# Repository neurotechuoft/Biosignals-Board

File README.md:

# Biosignals-Board

## Overview

The goal of this project is to build an EEG (electroencephalogram) signal acquisition pipeline for the "Fixed Challenge" portion of the NeurotechX Student competition taking place on March 18, 2018. The pipeline will consist of a biosignals board that is capable of picking up an analog EEG signal, perform analog to digital conversion and signal processing, and transmit the signal to a distant computer for real-time visualization and other applications.

### NeurotechX Competition Specifications

1. [Competition Website](https://neurotechx.github.io/studentclubs/competition/ "NeurotechX Competition")

## Project Plan
We will be developing during the summer and fall of 2017, targetting project completion by the end of 2017, leaving 3 months for additional testing and building upon the competition-ready project. The project is being organized into three subsections: analog signal acquistion and amplification, analog to digital conversion, and data transmission/software, which will all be developed concurrently. For analog to digital conversion, we will be using the Texas Instruments [ADS1299 ADC chip](./code/digital/README.md) to convert the acquired EEG signal.

## Project Progress
* Developed high-level schematic of entire system

## Excellent Resources
* [EEG PocketGuide](https://drive.google.com/file/d/0B4xsbDIeDmLPY3hObm1DVjV1TmM/view?usp=sharing)

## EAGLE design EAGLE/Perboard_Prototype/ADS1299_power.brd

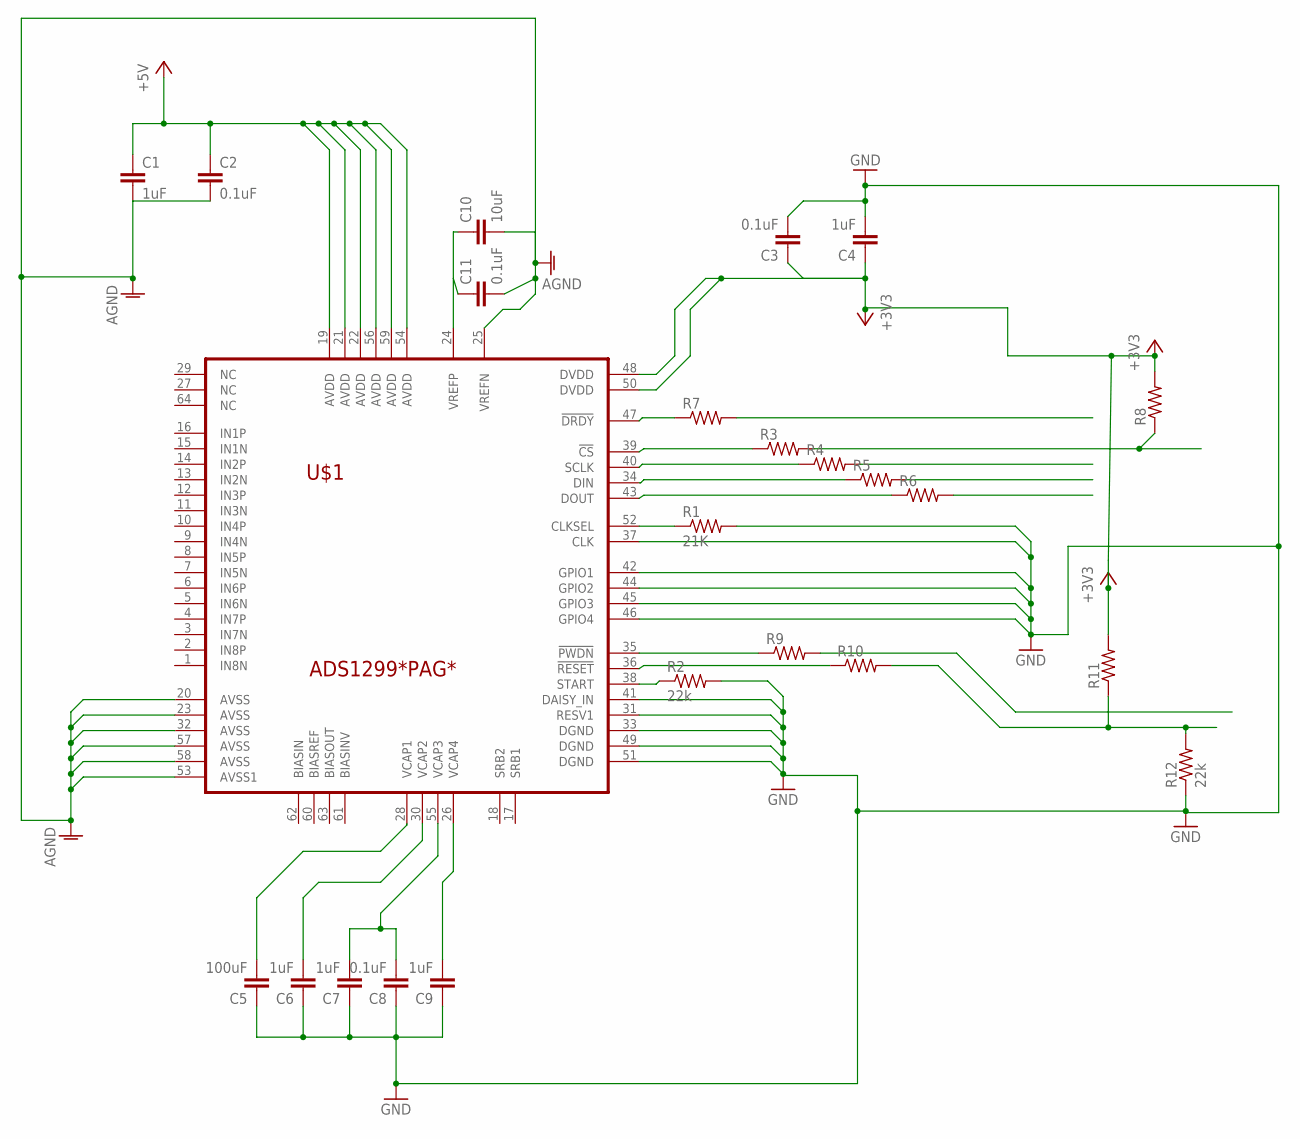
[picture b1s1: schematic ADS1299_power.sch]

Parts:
C1, C4, C6, C7, C9: 1uF; C2.5-3
C2, C3, C8, C11: 0.1uF; C2.5-3
C5: 100uF; C2.5-3
C10: 10uF; C2.5-3
R1: 21K; 0204V
R2, R12: 22k; 0204V
R3, R4, R5, R6, R7, R8, R9, R10, R11: R-US_0204/2V; 0204V
U$1: ADS1299*PAG*; TQFP64

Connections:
+3V3: C3.1, C4.1, R8.2, R11.2, U$1.48 (DVDD), U$1.50 (DVDD)
+5V: C1.1, C2.1, U$1.19 (AVDD), U$1.21 (AVDD), U$1.22 (AVDD), U$1.54 (AVDD), U$1.56 (AVDD), U$1.59 (AVDD)
AGND: C1.2, C2.2, C10.2, C11.2, U$1.20 (AVSS), U$1.23 (AVSS), U$1.25 (VREFN), U$1.32 (AVSS), U$1.53 (AVSS1), U$1.57 (AVSS), U$1.58 (AVSS)
GND: C3.2, C4.2, C5.1, C6.1, C7.1, C8.1, C9.1, R1.2, R2.2, R12.1, U$1.31 (RESV1), U$1.33 (DGND), U$1.37 (CLK), U$1.41 (DAISY_IN), U$1.42 (GPIO1), U$1.44 (GPIO2), U$1.45 (GPIO3), U$1.46 (GPIO4), U$1.49 (DGND), U$1.51 (DGND)
unnamed: C9.2, U$1.26 (VCAP4)
unnamed: C7.2, C8.2, U$1.55 (VCAP3)
unnamed: C10.1, C11.1, U$1.24 (VREFP)
unnamed: R1.1, U$1.52 (CLKSEL)
unnamed: C5.2, U$1.28 (VCAP1)
unnamed: R3.1, U$1.39 (!CS)
unnamed: R4.1, U$1.40 (SCLK)
unnamed: C6.2, U$1.30 (VCAP2)
unnamed: R2.1, U$1.38 (START)
unnamed: R5.1, U$1.34 (DIN)
unnamed: R6.1, U$1.43 (DOUT)
unnamed: R3.2, R8.1
unnamed: R7.1, U$1.47 (!DRDY)
unnamed: R10.1, U$1.36 (!RESET)
unnamed: R9.1, U$1.35 (!PWDN)
unnamed: R10.2, R11.1, R12.2

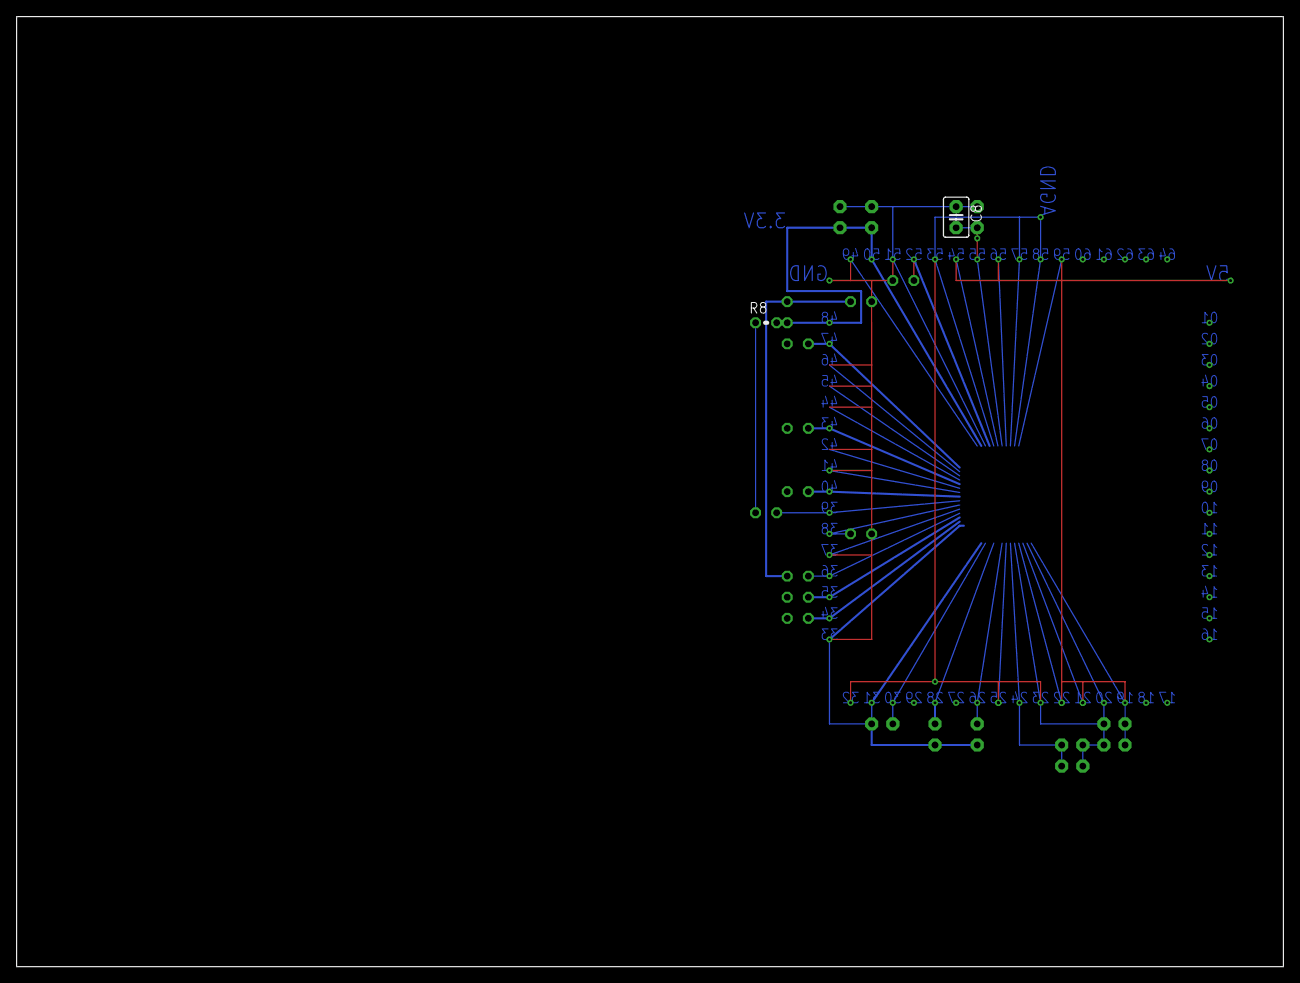
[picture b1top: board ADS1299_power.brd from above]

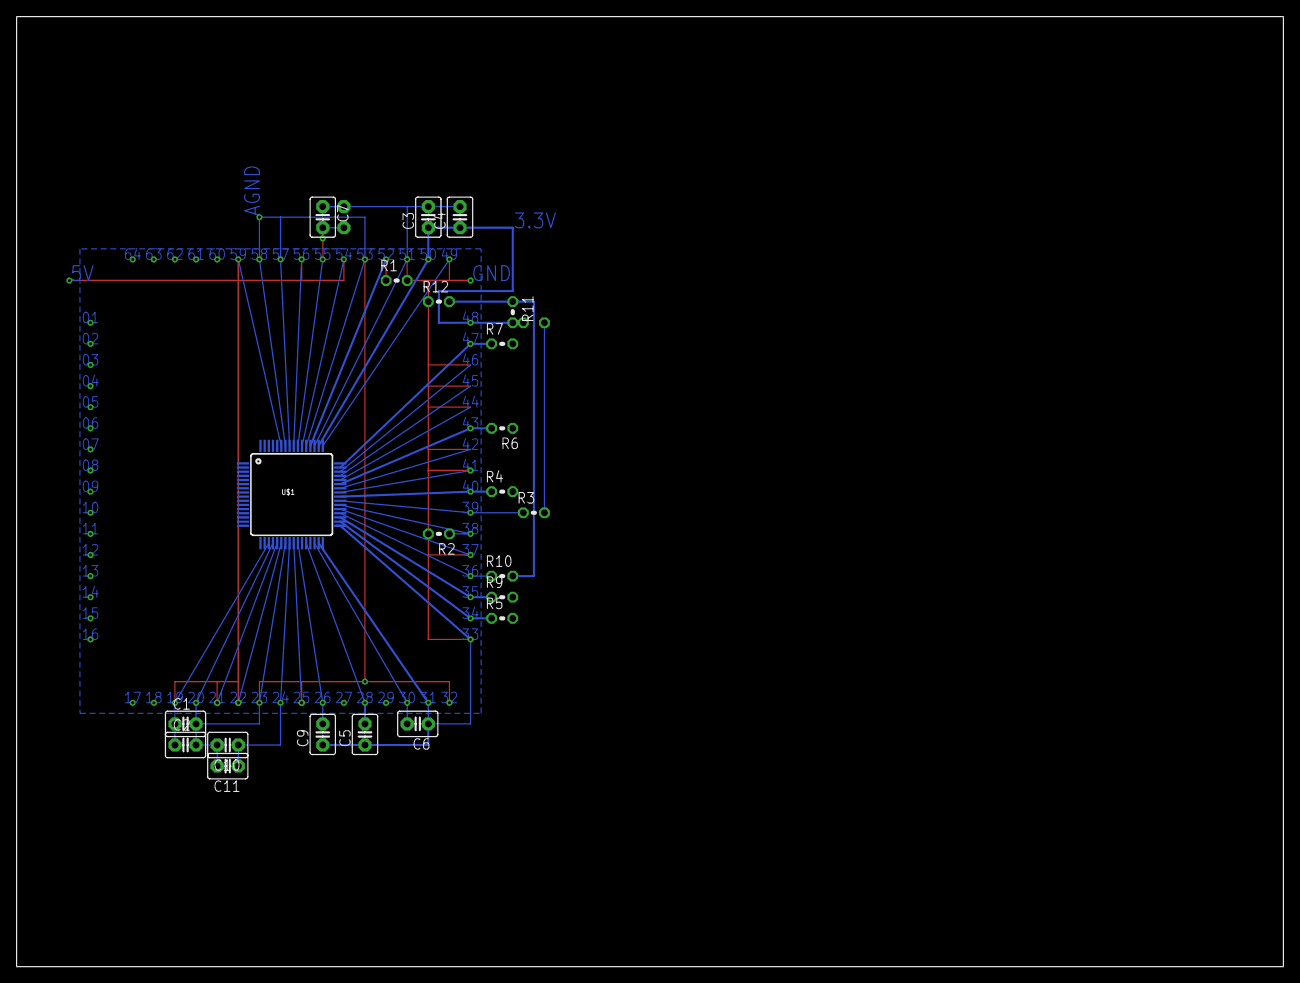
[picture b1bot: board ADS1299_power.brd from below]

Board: 2 copper layers, 152.4 x 114.3 mm, 24 parts (22 on the bottom side), 20 nets.

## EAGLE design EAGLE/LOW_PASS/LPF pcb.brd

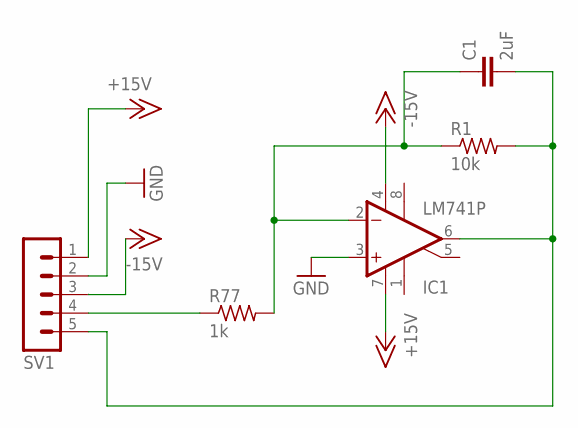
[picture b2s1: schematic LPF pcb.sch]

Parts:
C1: 2uF; C0603
IC1: LM741P; DIL08
R1: 10k; R0603
R77: 1k; R0603
SV1: MA05-1

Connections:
+15V: IC1.7 (V+), SV1.1
-15V: IC1.4 (V-), SV1.3
GND: IC1.3 (+IN), SV1.2
unnamed: R77.1, SV1.4
unnamed: C1.1, IC1.2 (-IN), R1.1, R77.2
unnamed: C1.2, IC1.6 (OUT), R1.2, SV1.5

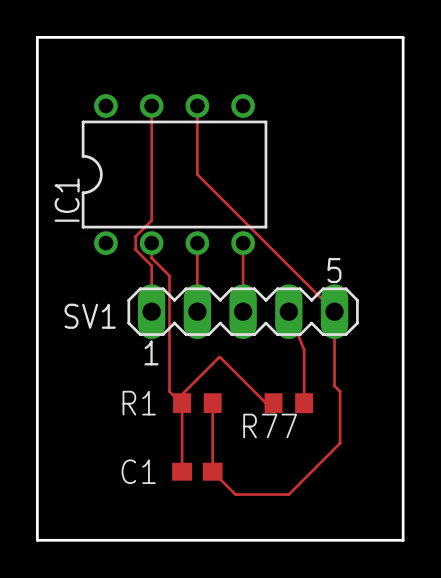
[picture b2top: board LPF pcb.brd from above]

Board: 2 copper layers, 20.3 x 27.9 mm, 5 parts (0 on the bottom side), 6 nets.

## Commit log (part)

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2016-10-05 Create New Folder
2016-10-06 Setting up a general overview and project plan. # Please enter the commit message for your changes. Lines starting # with '#' will be ignored, and an empty message aborts the commit. # # Committer: O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
2016-10-06 Setting up the overview structure for the project
2016-10-06 Formating overview design and adding TGAM section
2016-10-06 formatting
2016-10-06 Update README.md
    Future tasks
2016-10-06 attached arduino library for potential use
2016-10-06 Update README.md
    Documented all links from Oct. 5, 2016 meeting
2016-10-06 Meeting Notes updated
2016-10-08 Update README.md
    communications protocol
2016-11-01 Updating Project Progress
2016-11-15 testing bluetooth scanner
2016-11-15 added commenting
2017-04-03 Added requirements for 2017 competiton
2017-05-13 Updated competition rules link
2017-05-20 Repo update + planning schematic
2017-05-20 updated high level schematic
2017-05-20 showing image
2017-05-20 deleting old folders
2017-05-30 Updated meeting times
2017-06-01 updated meeting notes with tasks
2017-06-01 Pin and Register Config Spreadsheet
2017-06-01 organized files
2017-06-01 Organization of notes
2017-06-01 Passive filter hardware example
2017-06-01 added filter information
2017-06-01 Calculate frequency response + examples
2017-06-01 inculded EEG PocketGuide
2017-06-01 Passive Filter
2017-06-01 Included arduino signalgenerator
2017-06-01 included GoogleDrive link to EEG PocketGuide
2017-06-04 Added ADS1299 Arduino Library
2017-06-04 Modified .gitignore
2017-06-04 Deleted duplicate file Chip_Configuration.ods
2017-06-04 collapsed ADS1299 folder
2017-06-06 Filled in wiring connections for all pins
2017-06-06 Added more register information
2017-06-07 updated meeting notes
2017-06-08 Retrying previous commit: Added all pin connections
2017-06-08 Retrying commit: Added all wiring connections for all pins
2017-06-09 Removed ADS1299-Arduino library, will be replaced with OpenBCI Library
2017-06-09 Added OpenBCI ADS1299 Library
2017-06-09 updated meeting agendas
2017-06-10 restructure
2017-06-10 got rid of 2017 top folder
2017-06-10 Added code for bootup and converting test signal
2017-06-10 Updated .gitignore
2017-06-10 Implementign SPI on Arduino
2017-06-11 Reorganized pin chart and added diagram of pin connections
2017-06-11 Created Project_Timeline from General Meeting
2017-06-13 Added bootup and signal conversion code
2017-06-13 Arduinos communication
2017-06-17 Started agenda for Jun18 meeting
2017-06-17 Added resource for data transmission
2017-06-17 Re-formatted for Jun18 meeting agenda
2017-06-17 updated Raspberry Pi purchasing info
2017-06-18 Added to-do's to agenda
2017-06-18 Changed pin assignments to match our wiring
2017-06-18 Modified bootup code
2017-06-20 Updated Digital README
2017-06-20 Added meeting locations
2017-06-20 Started agenda for June 20 meeting
2017-06-20 Reformat meeting notes
2017-06-24 Added meeting notes for June 22
2017-06-28 Modified ADS1299 library to control PWDN pin and use Arduino SPI library
2017-06-28 Updated ads_bootup code to use modified ADS1299 library
2017-06-28 Recommiting ads_bootup, last commit not correct version
2017-06-29 Fixed bootup code
2017-06-30 Added June 28 meeting notes
2017-06-30 Updated meeting notes from June 17
2017-06-30 Added meeting notes for June 27
2017-07-02 Added functions for serial plotting and added our connections as defines in Definitions.h
2017-07-02 Experiment with Serial Plotter in Arduino IDE
2017-07-02 Added documentation and cleaned up code
2017-07-03 June 2nd session
2017-07-07 meeting Agenda for google Hangouts
2017-07-08 Updated meeting notes for July 7
2017-07-09 Started chart to track budget
2017-07-09 Started agenda for Sunday July 9 Meeting
2017-07-09 Added script to generate Meeting Notes template, work in progress
2017-07-09 updated TODOs
2017-07-09 included ##To-Do
2017-07-09 Cyton prog started doc
2017-07-11 Meeting notes for Design Studio
2017-07-19 notes from last meeting
2017-07-20 Naming
2017-07-23 Added summary of some key parameters and definitions in ADS1299 datasheet
2017-07-26 Added agenda and notes for Jul 26 meeting
2017-08-07 Moved and renamed Raspberry Pi Price research
2017-08-07 Fixed typos in pin connections
2017-08-07 Removed MicroSD card from 'To-buy' list and add to 'Purchased'
2017-08-07 Started Raspberry Pi Setup Notes
2017-08-08 Added ADSPacket class. This will be used when emulating ADS data
2017-08-08 Changed name of compiled executable
2017-08-08 Need to decide on meeting times
2017-08-09 Introductory meeting notes and next steps
2017-08-13 Meeting notes for Sunday Aug 13
2017-08-18 Started folder for hardware tests and added spi loopback test
2017-08-18 Reorganized RaspberryPi folder
2017-08-27 Add LPF Eagle project
2017-08-27 Removed LPF schematic.sch
2017-08-27 changed R2 to R77 made two reroutes
2017-08-28 Updated August 27 meeting notes
2017-08-30 Added ADS1299 datasheet for ease of access
2017-08-30 Updated pin connections in preparation for PCB
2017-08-31 Added meeting notes for Aug 30
2017-09-01 Minor updates to script
2017-09-03 Added section on default control register settings
2017-09-03 Started meeting notes for Sept 3
2017-09-03 Added ADS power schematic
2017-09-05 Updated meeting notes for Sept 03
2017-09-16 recruitment pdf
2017-09-17 Started meeting notes for September 17
2017-09-29 Renamed firmware folder to arduino-ads. Removed unused raspberrypi-ads library code
2017-09-29 Fixed incorrect data types
2017-09-29 Added comments and register descriptions
2017-10-02 Updaded schematic with open positions
2017-10-22 Reorganize repo - rename folders and files
2017-10-22 Reorganize repo: Move files into correct lib, src folders. Move analog, digital, and software folders under code/
2017-10-22 Move Musa's Arduino SPI code to src folder
2017-10-22 Added PDF version of competition rules
2017-10-23 Moved all previous meeting notes to the drive Converted from markdown to docx moved all scripts to admin/Summer2017/
2017-10-23 Restructured the code folder for Analog
2017-11-06 ADS1299_API bootup code
2017-11-07 Changed bootup delay time
2017-11-07 Implemented grid spacing. Added Frame. Need to route all the components
2017-11-08 Completed design for Protoboard Wiring.
2017-11-08 Re-wired pin 32 AGND
2017-11-09 Added .h file to .c
2017-11-09 Changed File Name
2017-11-09 Added .h file for ADS bcm bootup
2017-11-09 Fixed Minor Naming Error
2017-11-09 Updated EAGLE TODO and list of breakout pins
2017-11-10 Re-routed all sides and placed components on top
2017-11-11 Reorganized pins for breakout, differentiating perfboard and PCB
2017-11-11 Recomitting with latest version of BreakoutPins.txt
2017-11-12 Added register test function and reorganized functions to use ese519 library
2017-11-12 Moved main function from ADS1299_bcm2835 to main.c file
2017-11-12 Removed Meeting Notes section from README
2017-11-12 Add print statement for debuging
2017-11-12 Fix typo
2017-11-12 add carriage return
2017-11-13 restructure the code + modify makefile
2017-11-13 Fix function return type + Make File builds + completed source relocationing
2017-11-13 fixes compilation error
2017-11-13 add compatible bcm header
2017-11-13 add intermediate build folders
2017-11-14 add bcm implementation file
2017-11-14 Changed include definitions.h to include ADS1299_definitions.h
2017-11-14 Add bcm2835 .h and .c files to master
2017-11-14 Added functions to read registers and compare against their default values
2017-11-14 Add test_registers function call to main
2017-11-14 Add temporary compilation script. Will be replaced by Makefile
2017-11-15 Remove wiringPi files
2017-11-15 Fixed typo in _DEGUB_ ifdef. Added debug messages
2017-11-15 Clean up before the next rebuild
2017-11-15 Remove in tree inclusions
2017-11-15 Sync branch with build_devel branch
2017-11-15 Add more descriptive debug messages to test_register()
2017-11-18 Fix compilation warnings
2017-11-18 Rename variables and add comments to ads1299 library. Renamed test_register() to register_check() in ADS1299_bcm2835
2017-11-18 Added global state variable to keep track of whether ADS1299 is in RDATAC or SDATAC mode. Protects against improper access to registers while reading data
2017-11-18 Add line breaks to print messages when changing data mode
2017-11-18 Add line to verify data mode variable is working properly. Commented out because it is an optional test
2017-11-18 Added 4 TCLK delay after sending _SDATAC as required in datasheet
2017-11-18 Add script to combine make and running executable into one command
2017-11-21 Add further instructions for dependency setup
2017-11-21 Fix link styling in Readme doc
2017-11-27 Add decoder function and corresponding test function
2017-11-27 Added loop to main to reattempt bootup sequence up to 5 times if first attempt unsuccessful
2017-11-27 Add new-lines to print statements, and rename compile and run script
2017-11-27 plotter now plots sinusoidals, cleaned up app
2017-12-02 Add function to pulse pin at a set frequency
2017-12-02 Always save output of bootup to a log file
2017-12-02 Fix comment
2017-12-02 Add PWDN pin to definitions. Assign to GPIO pin 22
2017-12-02 Set PWDN pin to OUTPUT, and initialize pins to their default values as per the datasheet
2017-12-02 Remove duplicate ADS1299_init(). Add commented out test function to main
2017-12-02 Write PWDN pin to HIGH to boot-up. Change all delay() calls to delayMicroseconds(). Changed RESET pulse width to tRST from datasheet
2017-12-04 Change RESET pin from GPIO_J8_18 to GPIO_J8_16
2017-12-04 Correct Default DEVICE_ID to 0x1E for 8-channel ADS1299
2017-12-04 Fix checking criteria in register_check()
2017-12-04 Add initial version of ADS1299 - Arduino Emulator. Currently only verifies boot-up sequence
2017-12-04 hash and print config reg values
2017-12-04 add LICENSE file
2017-12-07 Update ADS1299_bcm2835.c
    Fixes typos and adds ID register read.
2017-12-07 Change to more elegant solution
2017-12-08 Add 3 GPIO pins as dedicated testing pins
2017-12-08 Re-structure program to decode ADS1299 RREG command to imitate on-chip register interface
2018-01-14 Fix compilation errors. Add other ADS1299 control pins
2018-01-14 Add defines for SPI pins and wiring details to comments
2018-01-14 Add logs folder to hold bootup logs
2018-01-14 Remove make compilation. Rename script accordingly
2018-01-14 Add setup script to set useful BSB environment variables
2018-01-15 Added functions to display states of GPIO pins. Fixed chip select polarity mistake
2018-01-15 Changed number of bootup attempts from 5 to 1
2018-01-21 Add line to open log file after finishing bootup
2018-01-21 Add print statements to display data mode changes between SDATAC, RDATAC, and RDATA
2018-01-21 Remove all software control of PIN_CS in code. Chip select is controlled by SPI hardware in bcm2835.
2018-01-27 Add functions to read and write specific register fields
2018-01-28 Correct code in ADS1299_write_register_field() to actually do SPI transfer
2018-01-28 Add register read/write test. Add test to bootup routine
2018-01-28 Add ability to process WREG commands from Raspberry Pi. Register interface now complete
2018-02-04 Minor change to account for new Codeblocks directory
2018-02-04 FIXME: Repurposed TEST_PIN_1 as PIN_RESET for testing purposes. Need to revert PIN_RESET to GPIO_J8_16 after testing
2018-02-04 Add 100 us delay between ADS1299_init() and ADS1299_bootup()
2018-02-04 Change PDREF_BUF config write from read-mask-write to write only. Increase reset pulse width to 500 us for testing
2018-02-05 Update comments
2018-02-05 Create README.md with directory structure
2018-02-07 Added power down and reboot functions
2018-02-07 Added command-line argument parsing to run different sequences. Add tests for bootup, register reading, SDATAC, and power cycling
2018-02-07 Add alias for run_neuro
2018-02-07 Pass bash arguments to ./bin/neuro
2018-02-13 Display pyqtgraph's built in Power Spectrum (fft)
2018-02-13 pyqtgraph included with gui code (need this version)
    had to edit a line in graphicsItems/PlotDataItem.py
